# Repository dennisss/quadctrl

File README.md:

Quadcopter Controller
=====================

**Deprecated: I'm keeping this up as it contains many good notes and code snippets for Android. Should you want a more complete and maintained platform, see https://github.com/dennisss/tansa**

TODO:
-----

- Move networking/xbee code out of 'creator'
- Abstract remote quadcopters as a ros node with a common command interface
- So, say have a Quadcopter class: a RosQuadcopter would be an implementation of that

Overview
--------

- An implementation of many common quadcopter control and modeling things

- An onboard controller with XBee support

- A GUI for controlling quadcopters from an XBee connected computer

- Support for motion capture systems
	- Drivers included for OptiTrack Motive

- Position and attitude control based on
	- `Minimum Snap Trajectory Generation and Control for Quadrotors` by Daniel Mellinger and Vijay Kumar

Useful Commands
---------------

- For creating an access point on a linux machine (requires create\_ap)
	- `sudo create_ap -n wlp3s0 MyAP helloworld`

- Starting up the controller
	- `ROS_IP=192.168.12.1 ROS_HOSTNAME=192.168.12.1 ./scripts/keyboard_ctrl.py`

- Checkout "Sharing internet connection over Ethernet" under https://wiki.archlinux.org/index.php/NetworkManager

	Scenario: your device has internet connection over wi-fi and you want to share the internet connection to other devices over ethernet.
	Requirements:
	Install the dnsmasq package to be able to actually share the connection.
	You internet connected device and the other devices are connected over a suitable ethernet cable (this usually means a cross over cable or a switch in between).
	Steps:
	Run nm-connection-editor from terminal.
	Add a new ethernet connection.
	Give it some sensible name. For example "Shared Internet"
	Go to "IPv4 Settings".
	For "Method:" select "Shared to other computers".
	Save
	Now you should have a new option "Shared Internet" under the Wired connections in NetworkManager.

- See `ext/cores/teensy3` for Teensy3 makefile example

- Programming AfroESCs: `make program_tgy_afro_nfet.0` via usb pwm programmer

- A good read for multicast implementation
	- http://www.tldp.org/HOWTO/Multicast-HOWTO-6.html

Builds
------

Below are descriptions of each of the builds:

- `dancer`
	- High performance acrobatic quadrotor for perfroming live performances as a dancer
	- Currently uses a Teensy 3 as an onboard controller with I2C
		- Teensy libraries need to be downloaded @ https://github.com/PaulStoffregen/cores
			- On Archlinux this requires the `arm-none-eabi-gcc` package for compiling
		- ESCs used are the AfroESC 20A slims with I2C wiring
			- Teensy I2C Lib: https://forum.pjrc.com/threads/21680-New-I2C-library-for-Teensy3
		- Firmware for ESCS: https://github.com/balrog-kun/tgy
			- http://www.rcgroups.com/forums/showthread.php?t=1955848
			- http://www.rcgroups.com/forums/showthread.php?t=2032252

Libraries Used
--------------

- XBee Support via `https://github.com/attie/libxbee3`
	- Needs to be compiled with escaping mode enabled
- Arduino/Teensy version @ `https://github.com/andrewrapp/xbee-arduino`
- I2C Library: `https://github.com/jrowberg/i2cdevlib.git`
- I2C Teensy Addon: `https://github.com/nox771/i2c_t3`

- OGRE into QT5
	- http://www.ogre3d.org/tikiwiki/tiki-index.php?page=Integrating+Ogre+into+QT5

Drivers
-------

- OptiTrack
	- Included is a driver for interfacing with OptiTrack Motive 1.9.0 via the NatNet SDK 2.9.0
	- Unix implementation of the NatNetClient with same interface as the SDK

Android
-------

Included is a fully functional Android implementation of the controller which can turn any smartphone into a quadcopter controller (with some additional USB hardware).

- Disclaimer: this is active research code; safety and functionality are not guranteed. Please observe caution while testing.
- Android Phone powered Quadcopter (with ROS for remote control)
- Compatible with Android 6.0 stock. No root required.
- Connects to motors via a USB cable connected to an Arduino (see arduino/arduino.ino)
- Requires rosjava with android_core to be installed on the computer (you need to change app/build.gradle to point to these packages)
- Uses custom versions of libftdi and libusb (included)

- For compiling, you need to separately compile `roscpp_android_ndk` and place it in the `ext` folfer

- TODO: Add video streaming
	- Combine the native mvision code using the capture request to go to many places.
	- One of which should be like https://github.com/fyhertz/libstreaming

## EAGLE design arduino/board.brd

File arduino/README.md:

QuadCtrl Hardware
=================

Motor Configuration
-------------------

- Motor 1 is in the top left and should spin clockwise. The numbering of motors is clockwise (motor 4 is bottom left).

Interface Board
---------------

A USB board used to control the motors, and read any external sensors. It uses an 115200 baud serial connection over USB to transmit motor commands.

- See the included Eagle CAD schematics in this folder
	- Designed for mounting under DJI F450 top plate
	- It includes circuitry for measuring rough 3S lipo battery voltage via an Arduino analog pin
	- Note: the throughhole components should be mounted on the bottom side
	- Uses an Adafruit Metro Mini
	- Connect the jumper to power the USB device with the UBEC

- Some implementation notes
	- Kills motors if no serial motor command is received within < 1s. It expects a > 100Hz motor update rate from the controller.
	- To prevent accidental re-arming of the motors, the board is powered by an UBEC connected to the motor battery. This way the ESCs are armed exactly once at battery connection and stay ready after plugging/unpluging phones. Note: the included design assumes OPTO ESCs

- It is recommended to use an Adafruit Metro Mini, Arduino Micro, or Arduino Pro Mini (NOT a Pro Micro)
	- TLDR: The Atmega board needs to be Arduino compatible and have Digital pins 3,9,10,11, at least one analog pin, and on board USB-serial.
	- Use PWM @ 490Hz to control each ESC
	- See the `arduino.ino` sketch. You may need to change the pin numbers to match your board and motor ordering
	- Warning: Do not use Arduino pins 5,6 to control the ESCs; on many boards, they run on a different clock that is at the wrong speed.

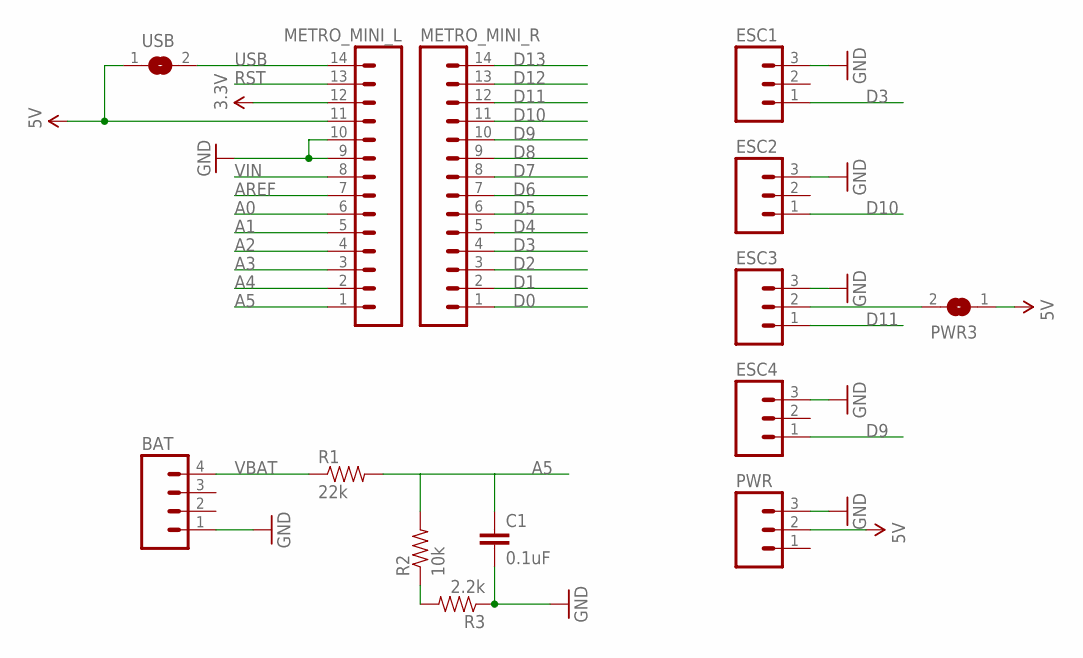
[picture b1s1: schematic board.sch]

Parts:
BAT: M04POLAR; MOLEX-1X4
C1: 0.1uF; AXIAL-5MM
ESC1, ESC2, ESC3, ESC4: M03POLAR; MOLEX-1X3
METRO_MINI_L: M14; 1X14
METRO_MINI_R: M14; 1X14
PWR: M03POLAR; MOLEX-1X3
PWR3: SJW
R1: 22k; AXIAL-0.4
R2: 10k; AXIAL-0.4
R3: 2.2k; AXIAL-0.4
USB: SJW

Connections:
3.3V: METRO_MINI_L.12
5V: METRO_MINI_L.11, PWR.2, PWR3.1, USB.1
A0: METRO_MINI_L.6
A1: METRO_MINI_L.5
A2: METRO_MINI_L.4
A3: METRO_MINI_L.3
A4: METRO_MINI_L.2
A5: C1.P$1 (1), METRO_MINI_L.1, R1.P$2 (2), R2.P$2 (2)
AREF: METRO_MINI_L.7
D0: METRO_MINI_R.1
D1: METRO_MINI_R.2
D2: METRO_MINI_R.3
D3: ESC1.1, METRO_MINI_R.4
D4: METRO_MINI_R.5
D5: METRO_MINI_R.6
D6: METRO_MINI_R.7
D7: METRO_MINI_R.8
D8: METRO_MINI_R.9
D9: ESC4.1, METRO_MINI_R.10
D10: ESC2.1, METRO_MINI_R.11
D11: ESC3.1, METRO_MINI_R.12
D12: METRO_MINI_R.13
D13: METRO_MINI_R.14
GND: BAT.1, C1.P$2 (2), ESC1.3, ESC2.3, ESC3.3, ESC4.3, METRO_MINI_L.9, METRO_MINI_L.10, PWR.3, R3.P$1 (1)
unnamed: R2.P$1 (1), R3.P$2 (2)
unnamed: ESC3.2, PWR3.2
RST: METRO_MINI_L.13
USB: METRO_MINI_L.14, USB.2
VBAT: BAT.4, R1.P$1 (1)
VIN: METRO_MINI_L.8

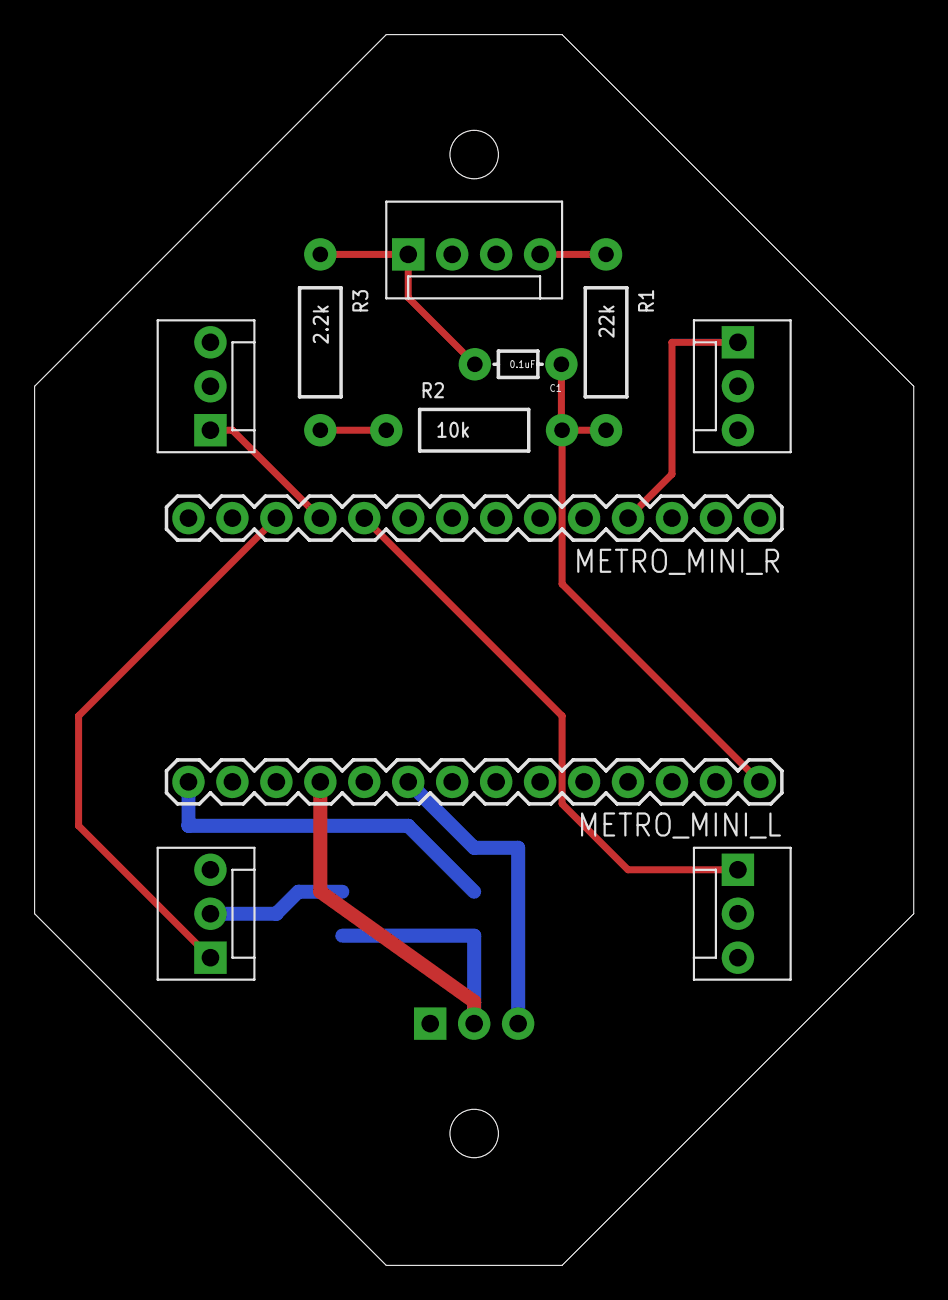
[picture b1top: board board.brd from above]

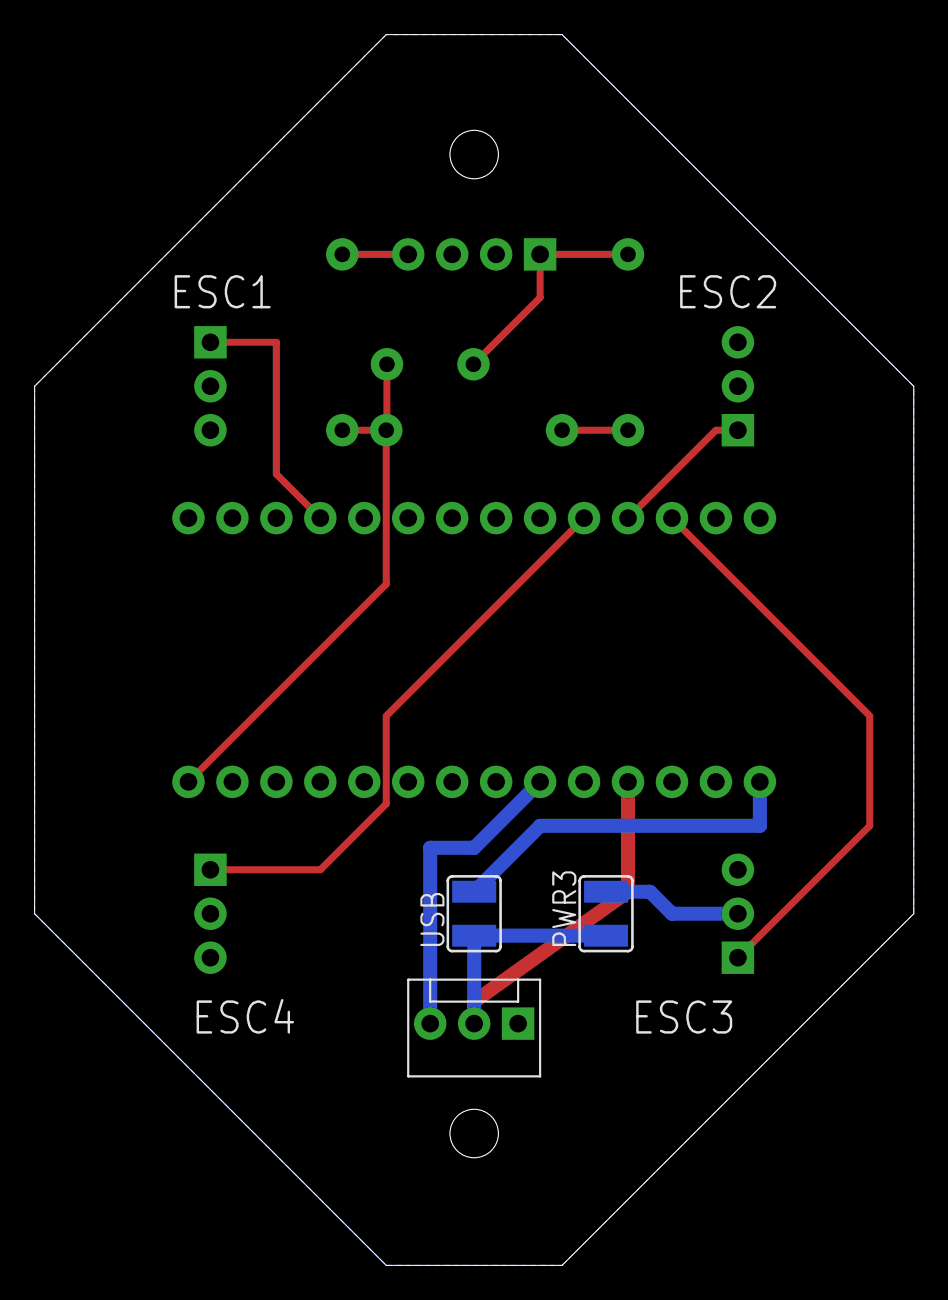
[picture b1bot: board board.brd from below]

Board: 2 copper layers, 50.8 x 71.1 mm, 14 parts (3 on the bottom side), 11 nets.

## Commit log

2015-12-15 Get most of the controller working
2015-12-17 Use ros params for gains
2015-12-18 Renaming
2015-12-23 Change UI and add gyro calibration
2015-12-27 Separate Android code and add simulation
2015-12-27 Move the Android specific libraries
2015-12-27 Rework some old code
2015-12-29 Add hardware interface board schematics
2015-12-30 Flip board and make ready to build
2016-01-03 Simulation improvements and change serial protocol
2016-02-12 Add onboard controller and creator
2016-02-17 Add initial OptiTrack driver
2017-01-18 Add notice

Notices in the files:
parts and their libraries:
SparkFun-Connectors: Licensing: Creative Commons ShareAlike 4.0 International - https://creativecommons.org/licenses/by-sa/4.0
